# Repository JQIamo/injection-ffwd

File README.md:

# Injection FFWD

Based on this paper: [Active stabilization of a diode laser injection lock](http://dx.doi.org/10.1063/1.4953589)
arXiv version: https://arxiv.org/abs/1602.03504

Basic idea: measure the laser peak height on a fabry perot cavity and feed forward to the injection current to maximize the peak height (ie, maintain it in a stable injection locked region)

Implements a crude servo algorithm with auto-relock feature.

Todo:

* status of lock to computer control (pause cycle if in auto-relock)
* ...?

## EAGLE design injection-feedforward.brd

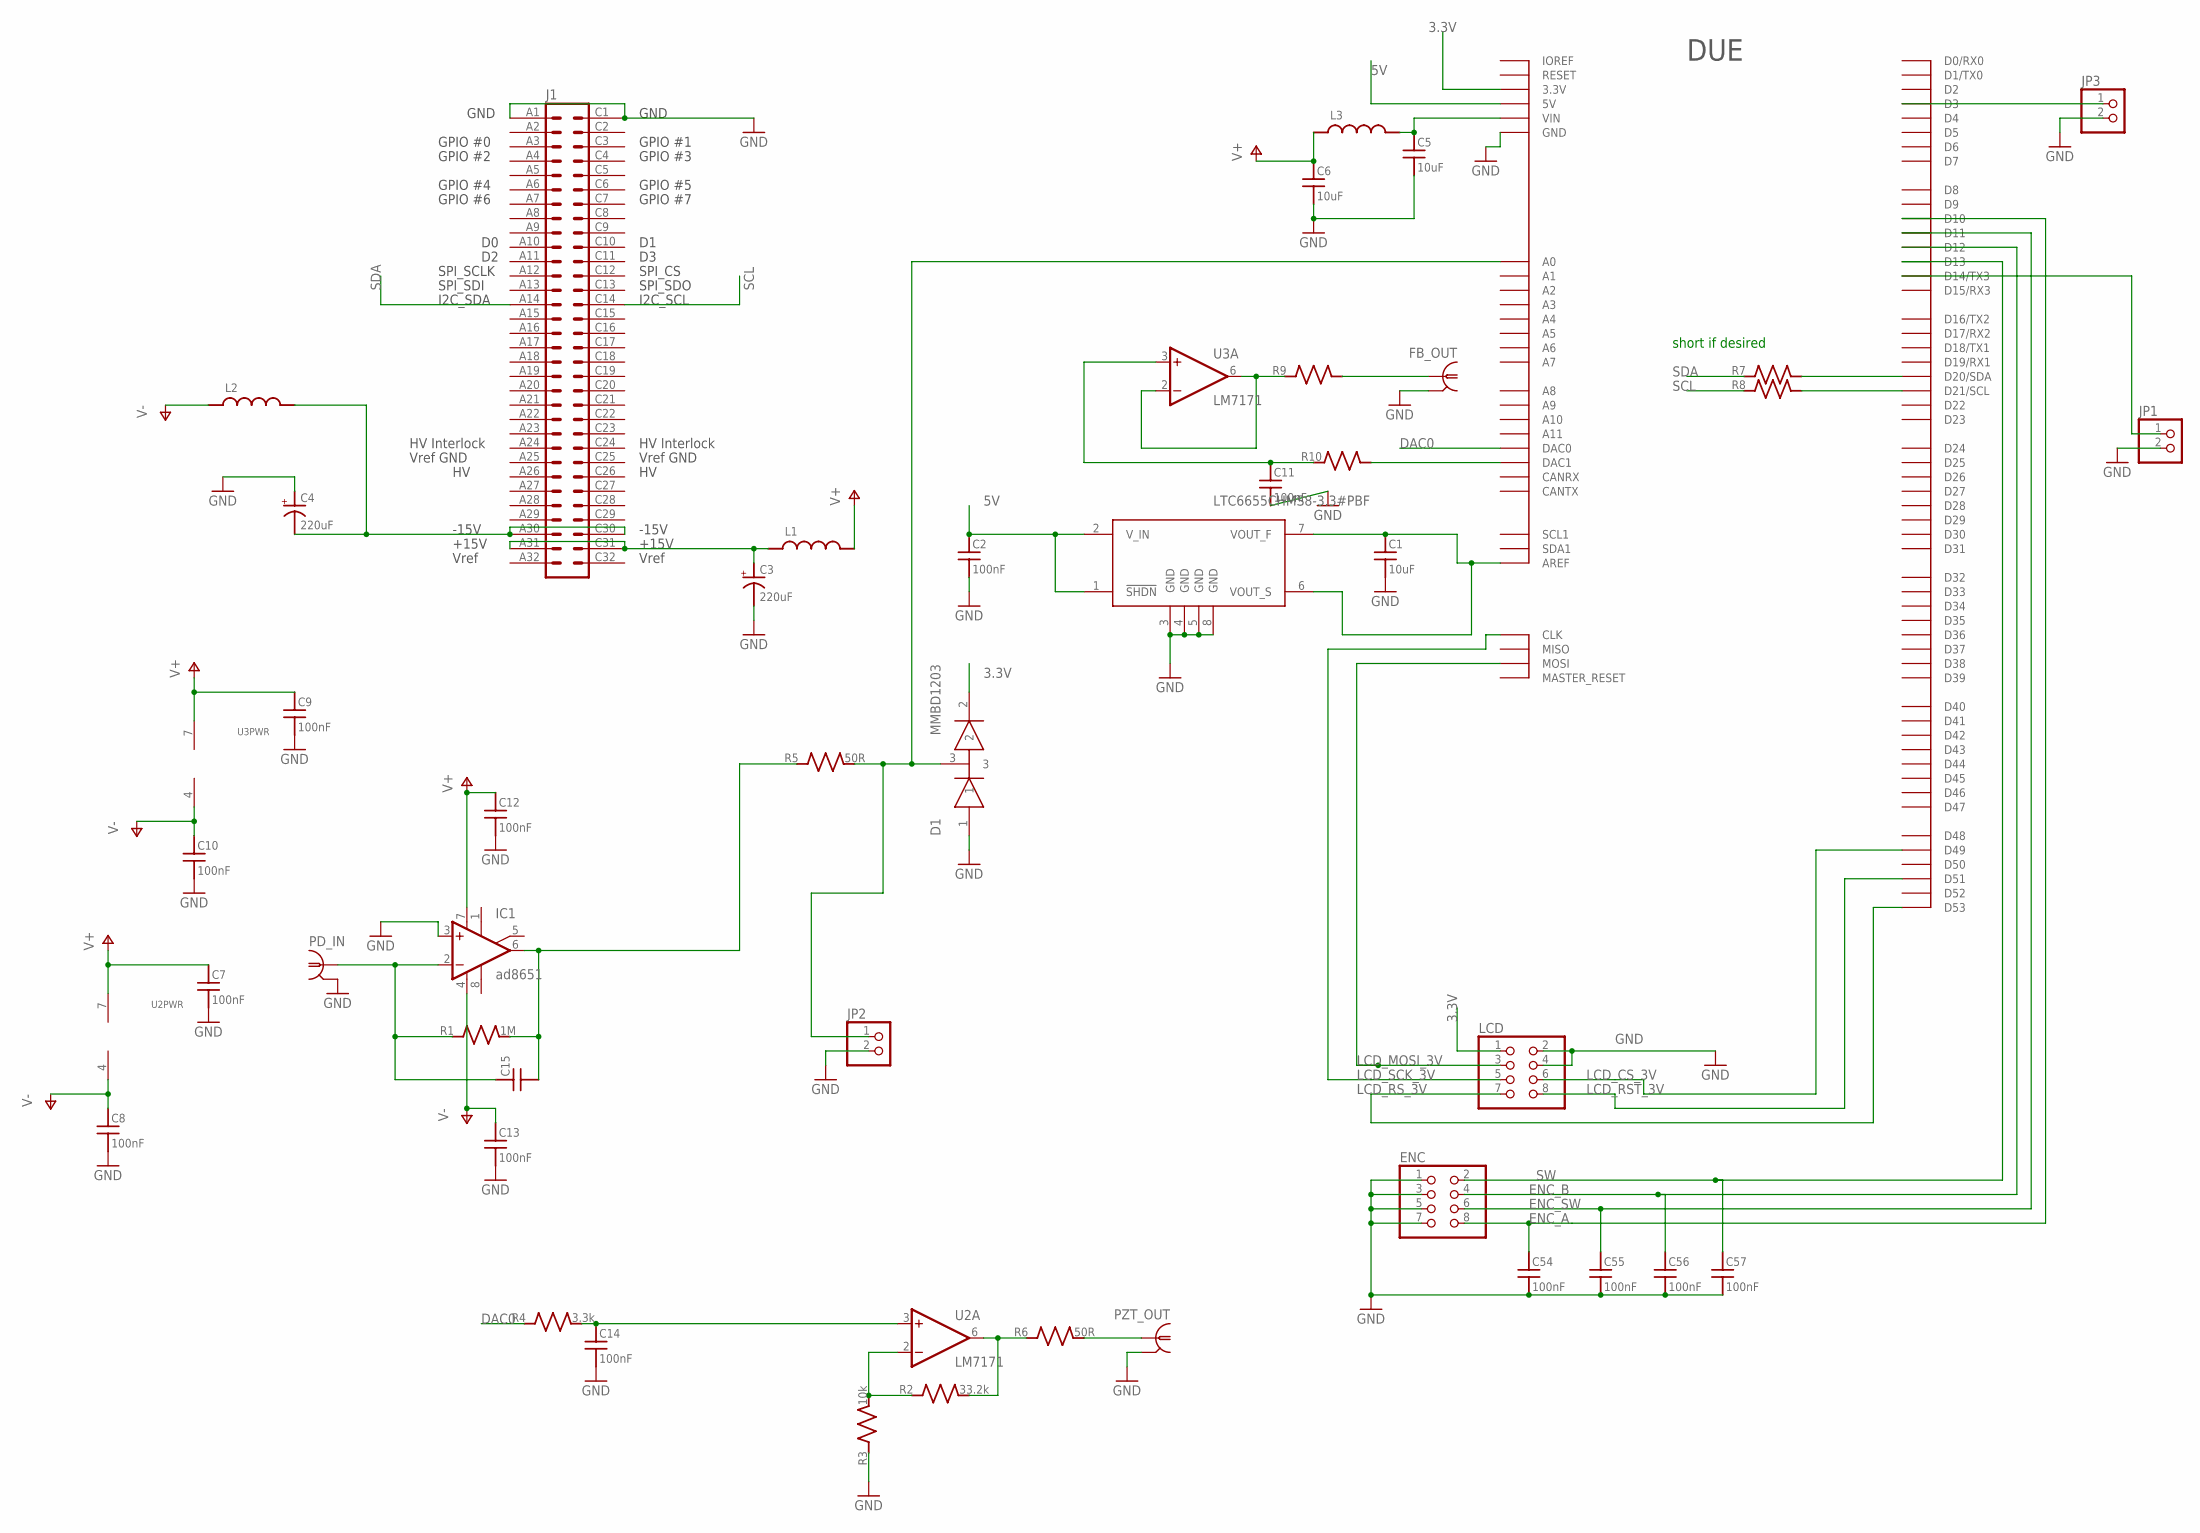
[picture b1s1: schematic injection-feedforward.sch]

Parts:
C1, C5, C6: 10uF; C_MLCC_0805
C2, C7, C8, C9, C10, C11, C12, C13, C14: 100nF; C_MLCC_0603
C3, C4: 220uF; PANASONIC_F
C15: C_MLCC_SMDCMLCC_0603; C_MLCC_0603
C54, C55, C56, C57: 100nF; C_MLCC_0603; PARTNO 1276-1936-1-ND
D1: MMBD1203; SOT23
ENC: PINHD-2X4-SHROUD; ML08; PARTNO 609-3530-ND
FB_OUT: BNC-H; BNC90
IC1: ad8651; SO08
J1: VG64C; VG64-CUTOUT
JP1, JP2, JP3: PINHD-1X2; 1X02
L1, L2, L3: L_FERRITE_SMDLFERRITE_0603; L_FERRITE_0603
LCD: PINHD-2X4-SHROUD; ML08; PARTNO 609-3530-ND
PD_IN: BNC-H; BNC90
PZT_OUT: BNC-H; BNC90
R1: 1M; R_0603
R2: 33.2k; R_0603
R3: 10k; R_0603
R4: 3.3k; R_0603
R5, R6: 50R; R_0603
R7, R8, R9, R10: R_SMDR0603; R_0603
U1: LTC6655CHMS8-3.3#PBF; MSOP8
U2, U3: LM7171; SO08$1
U$1: DUE_SHIELD

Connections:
3.3V: D1.2, LCD.1, U$1.3.3 (3.3V)
5V: C2.P$1 (1), U1.1 (!SHDN), U1.2 (V_IN), U$1.5V0 (5V), U$1.5V1 (5V), U$1.5V2 (5V), U$1.5V3 (5V)
DAC0: R4.P$1 (1), U$1.DAC0
ENC_A: C54.P$1 (1), ENC.8, U$1.10 (D10)
ENC_B: C56.P$1 (1), ENC.4, U$1.12 (D12)
ENC_SW: C55.P$1 (1), ENC.6, U$1.11 (D11)
GND: C1.P$2 (2), C2.P$2 (2), C3.-, C4.+, C5.P$2 (2), C6.P$2 (2), C7.P$2 (2), C8.P$2 (2), C9.P$2 (2), C10.P$2 (2), C11.P$2 (2), C12.P$2 (2), C13.P$2 (2), C14.P$2 (2), C54.P$2 (2), C55.P$2 (2), C56.P$2 (2), C57.P$2 (2), D1.1, ENC.1, ENC.3, ENC.5, ENC.7, FB_OUT.2, IC1.3 (+IN), J1.A1, J1.C1, JP1.2, JP2.2, JP3.2, LCD.2, LCD.4, PD_IN.2, PZT_OUT.2, R3.P$1 (1), U1.3 (GND), U1.4 (GND), U1.5 (GND), U1.8 (GND), U$1.GND, U$1.GND0 (GND), U$1.GND1 (GND), U$1.GND2 (GND), U$1.GND3 (GND), U$1.GND4 (GND)
LCD_CS_3V: LCD.6, U$1.49 (D49)
LCD_MOSI_3V: LCD.3, U$1.MOSI
LCD_RST_3V: LCD.8, U$1.51 (D51)
LCD_RS_3V: LCD.7, U$1.53 (D53)
LCD_SCK_3V: LCD.5, U$1.CLK
unnamed: C1.P$1 (1), U1.6 (VOUT_S), U1.7 (VOUT_F), U$1.AREF
unnamed: C3.+, J1.A31, J1.C31, L1.P$1 (1)
unnamed: C4.-, J1.A30, J1.C30, L2.P$2 (2)
unnamed: R7.P$2 (2), U$1.20 (D20/SDA)
unnamed: R9.P$1 (1), U3.2 (-IN), U3.6 (OUT)
unnamed: C5.P$1 (1), L3.P$2 (2), U$1.VIN
unnamed: R2.P$1 (1), R3.P$2 (2), U2.2 (-IN)
unnamed: R2.P$2 (2), R6.P$1 (1), U2.6 (OUT)
unnamed: C15.P$1 (1), IC1.2 (-IN), PD_IN.1, R1.P$1 (1)
unnamed: C15.P$2 (2), IC1.6 (OUT), R1.P$2 (2), R5.P$1 (1)
unnamed: C14.P$1 (1), R4.P$2 (2), U2.3 (+IN)
unnamed: JP1.1, U$1.14 (D14/TX3)
unnamed: D1.3, JP2.1, R5.P$2 (2), U$1.A0
unnamed: PZT_OUT.1, R6.P$2 (2)
unnamed: R8.P$2 (2), U$1.21 (D21/SCL)
unnamed: FB_OUT.1, R9.P$2 (2)
unnamed: C11.P$1 (1), R10.P$1 (1), U3.3 (+IN)
unnamed: R10.P$2 (2), U$1.DAC1
unnamed: JP3.1, U$1.3 (D3)
SCL: J1.C14, R8.P$1 (1)
SDA: J1.A14, R7.P$1 (1)
SW: C57.P$1 (1), ENC.2, U$1.13 (D13)
V+: C6.P$1 (1), C7.P$1 (1), C9.P$1 (1), C12.P$1 (1), IC1.7 (V+), L1.P$2 (2), L3.P$1 (1), U2.7 (V+), U3.7 (V+)
V-: C8.P$1 (1), C10.P$1 (1), C13.P$1 (1), IC1.4 (V-), L2.P$1 (1), U2.4 (V-), U3.4 (V-)

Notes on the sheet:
short if desired

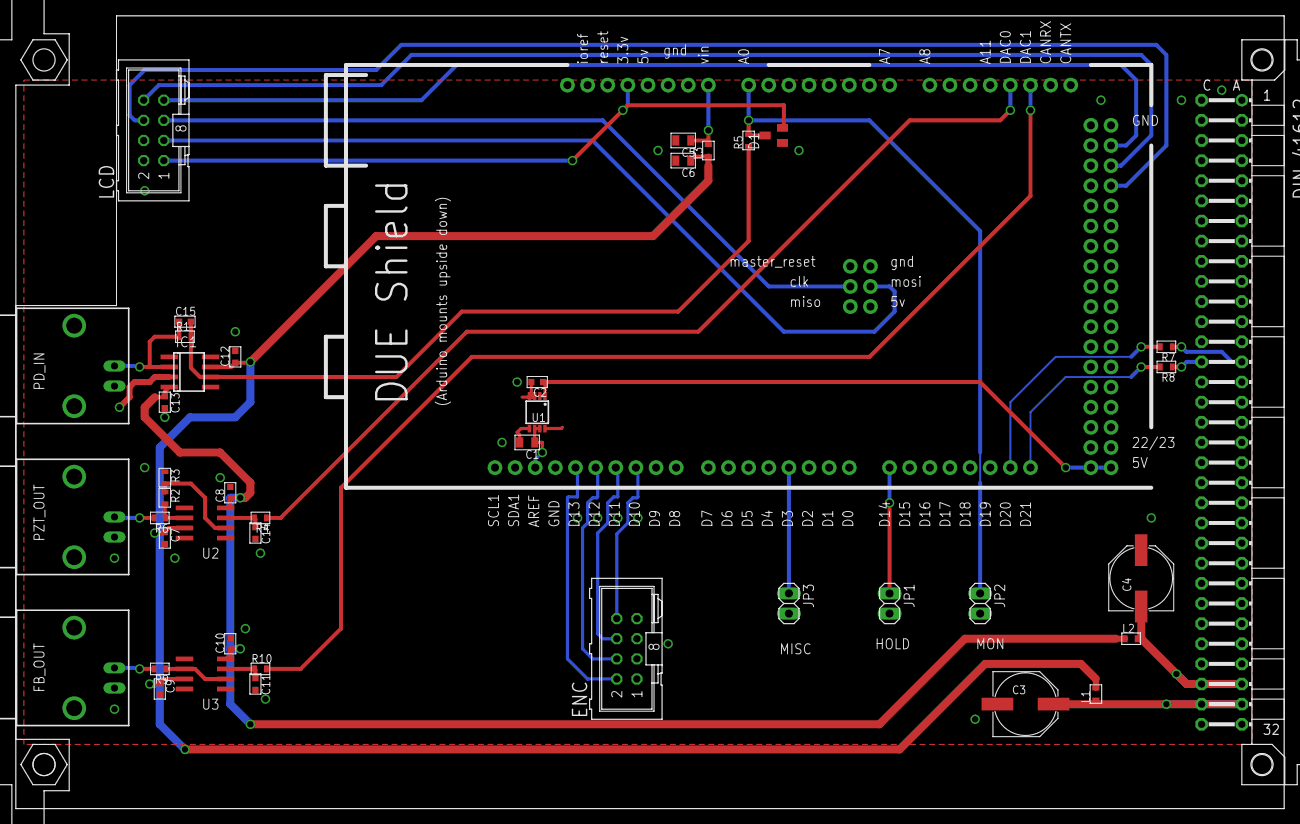
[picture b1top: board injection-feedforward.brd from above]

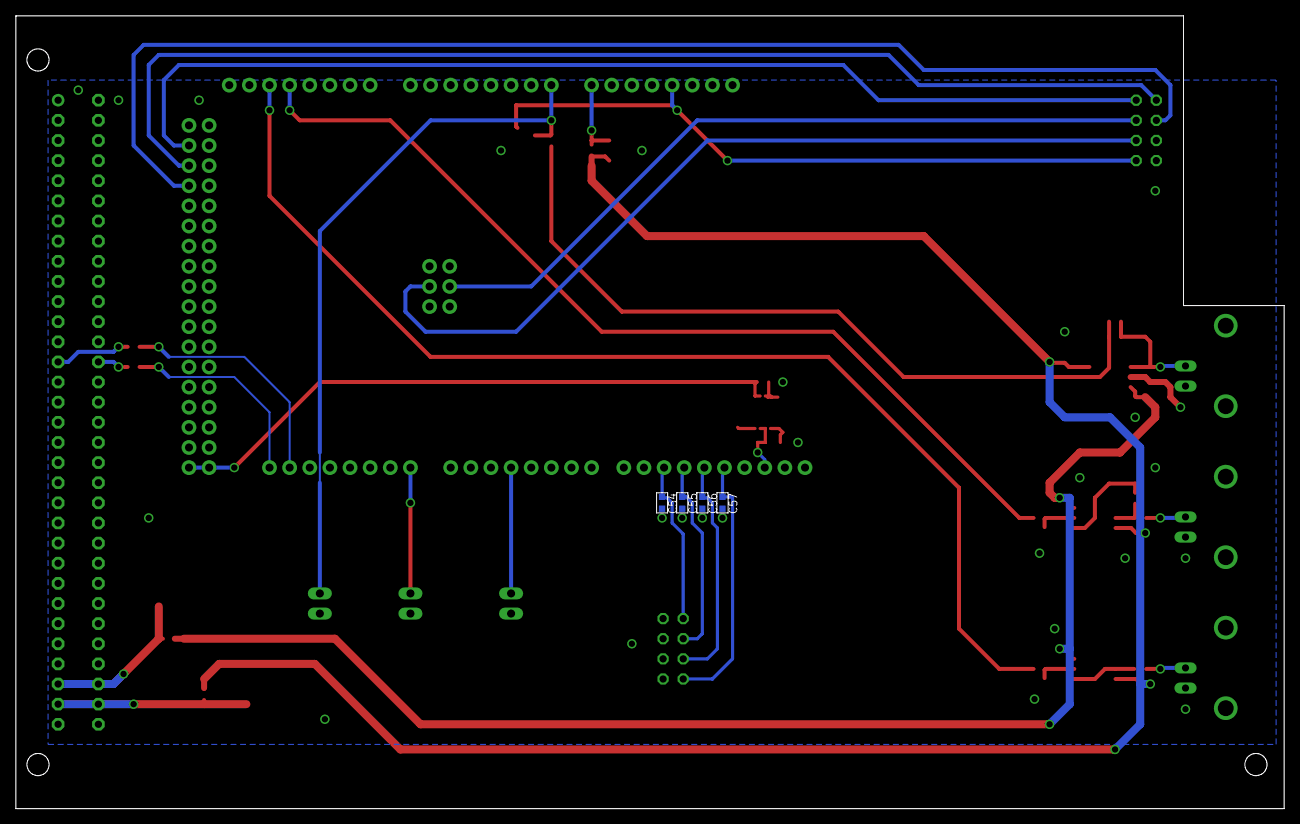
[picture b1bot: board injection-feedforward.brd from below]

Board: 2 copper layers, 160.0 x 100.0 mm, 47 parts (4 on the bottom side), 36 nets.

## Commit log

2016-10-08 Initial board design
    Has some defects:
    * need to power PD op amp at 5V not +/-15V
2016-10-08 initial code commit; mostly working
    * still need to implement display, rotary encoder
    * eventual integration over backplane?
2016-10-08 added readme
2016-10-08 Moved libraries to subfolder; few changes"
